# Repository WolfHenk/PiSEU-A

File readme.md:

THE SEU (Sende-Empfangs-Umsetzer) translates TW39 to ED1000 and vice versa

SEU-A was at "Amt" the networks side of the line. SEU-B was at the telex at costumers side.

This card emulates SEU-A and sits between raspberry Pi (piTelex) and a ED1000 and works as a kind of modem between piTelex TXD and RXD and Telex

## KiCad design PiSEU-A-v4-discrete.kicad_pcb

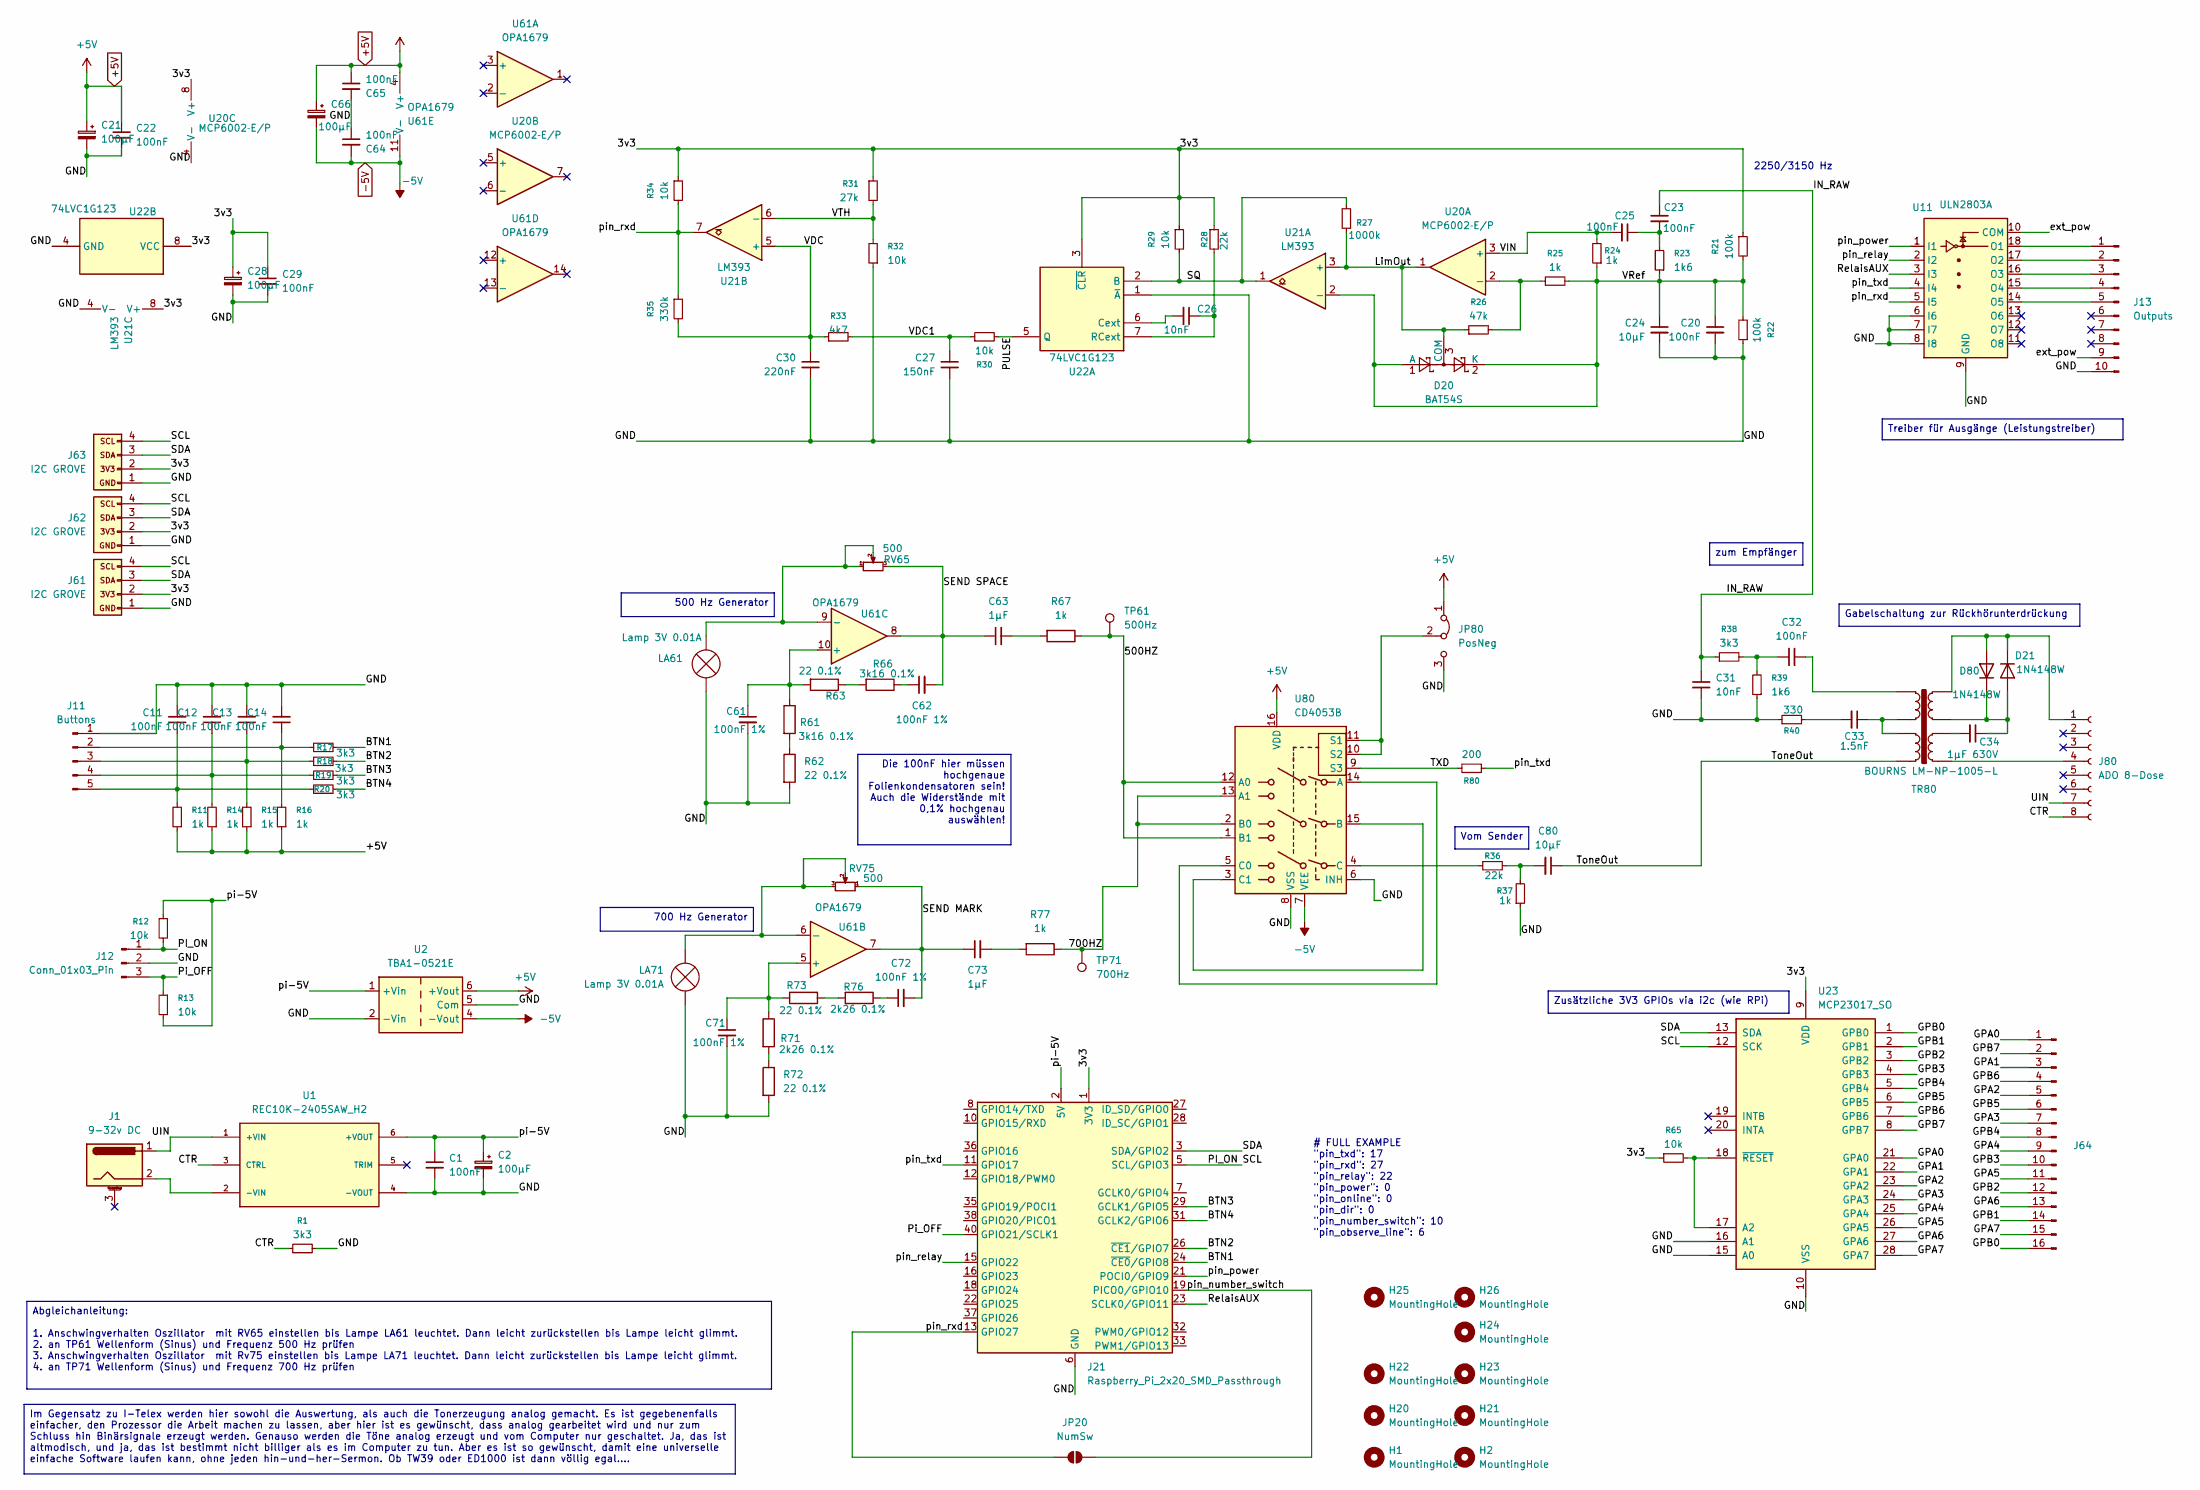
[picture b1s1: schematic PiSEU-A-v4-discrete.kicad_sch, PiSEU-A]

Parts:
C1, C11, C12, C13, C14, C20, C22, C23, C25, C29, C32, C64, C65: 100nF; C_Disc_D4.7mm_W2.5mm_P5.00mm; JLCPCB Part # C1590
C2, C21, C28: 100µF; CP_Radial_D6.3mm_P2.50mm; JLCPCB Part # C3338
C24, C80: 10µF; C_Radial_D5.0mm_H7.0mm_P2.00mm
C26, C31: 10nF; C_Disc_D5.0mm_W2.5mm_P2.50mm
C27: 150nF; C_Rect_L7.0mm_W4.5mm_P5.00mm; JLCPCB Part # C1597
C30: 220nF; C_Rect_L7.0mm_W4.5mm_P5.00mm; JLCPCB Part # C21120
C33: 1.5nF; C_Disc_D4.7mm_W2.5mm_P5.00mm; Part Number ggtt; JLCPCB Part # C1595
C34: 1µF 630V; C_Rect_L41.5mm_W15.0mm_P37.50mm_MKS4
C61, C62, C71, C72: 100nF 1%; C_Disc_D8.0mm_W2.5mm_P5.00mm
C63, C73: 1µF; C_Rect_L4.6mm_W3.8mm_P2.50mm_MKS02_FKP02; JLCPCB Part # C15849
C66: 100µF; CP_Radial_D6.3mm_P2.50mm
D20: BAT54S; SOT-23
D21, D80: 1N4148W; D_DO-35_SOD27_P7.62mm_Horizontal
H1, H2, H20, H21, H22, H23, H24, H25, H26: MountingHole; MountingHole_3.2mm_M3
J1: 9-32v DC; BarrelJack_Wuerth_6941xx301002
J11: Buttons; PinHeader_1x05_P2.54mm_Vertical
J12: Conn_01x03_Pin; PinHeader_1x03_P2.54mm_Vertical
J13: Outputs; PinHeader_2x05_P2.54mm_Vertical
J21: Raspberry_Pi_2x20_SMD_Passthrough; Raspberry_Pi_Zero_Socketed_THT_FaceDown_MountingHoles
J61, J62, J63: I2C GROVE; NS-Tech_Grove_1x04_P2mm_Vertical
J64: I2C-OUTPUTS; PinHeader_2x08_P2.54mm_Vertical; Part Number 1-1602FBV0T
J80: ADO 8-Dose; PinHeader_1x08_P2.54mm_Vertical
JP20: NumSw; SolderJumper-2_P1.3mm_Open_RoundedPad1.0x1.5mm
JP80: PosNeg; SolderJumper-3_P1.3mm_Bridged12_Pad1.0x1.5mm
LA61, LA71: Lamp 3V 0.01A; SolderWire-0.5sqmm_1x02_P4.6mm_D0.9mm_OD2.1mm
R1, R17, R18, R19, R20, R38: 3k3; R_Axial_DIN0207_L6.3mm_D2.5mm_P7.62mm_Horizontal; JLCPCB Part # C22978
R11, R14, R15, R16, R24, R25, R37, R67, R77: 1k; R_Axial_DIN0207_L6.3mm_D2.5mm_P7.62mm_Horizontal; JLCPCB Part # C21190
R12, R13, R29, R30, R32, R34, R65: 10k; R_Axial_DIN0207_L6.3mm_D2.5mm_P7.62mm_Horizontal; JLCPCB Part # C25804
R21, R22: 100k; R_Axial_DIN0207_L6.3mm_D2.5mm_P7.62mm_Horizontal; JLCPCB Part # C25803
R23, R39: 1k6; R_Axial_DIN0207_L6.3mm_D2.5mm_P7.62mm_Horizontal
R26: 47k; R_Axial_DIN0207_L6.3mm_D2.5mm_P7.62mm_Horizontal; JLCPCB Part # C25600
R27: 1000k; R_Axial_DIN0207_L6.3mm_D2.5mm_P7.62mm_Horizontal; JLCPCB Part # C22935
R28, R36: 22k; R_Axial_DIN0207_L6.3mm_D2.5mm_P7.62mm_Horizontal; JLCPCB Part # C31850
R31: 27k; R_Axial_DIN0207_L6.3mm_D2.5mm_P7.62mm_Horizontal; JLCPCB Part # C22967
R33: 4k7; R_Axial_DIN0207_L6.3mm_D2.5mm_P7.62mm_Horizontal
R35: 330k; R_Axial_DIN0207_L6.3mm_D2.5mm_P7.62mm_Horizontal
R40: 330; R_Axial_DIN0207_L6.3mm_D2.5mm_P7.62mm_Horizontal; JLCPCB Part # C23138
R61, R66: 3k16 0.1%; R_Axial_DIN0207_L6.3mm_D2.5mm_P7.62mm_Horizontal
R62, R63, R72, R73: 22 0.1%; R_Axial_DIN0207_L6.3mm_D2.5mm_P7.62mm_Horizontal
R71, R76: 2k26 0.1%; R_Axial_DIN0207_L6.3mm_D2.5mm_P7.62mm_Horizontal
R80: 200; R_Axial_DIN0207_L6.3mm_D2.5mm_P7.62mm_Horizontal; JLCPCB Part # C8218
RV65, RV75: 500; Potentiometer_Bourns_3386P_Vertical
TP61: 500Hz; TestPoint_Pad_1.0x1.0mm
TP71: 700Hz; TestPoint_Pad_1.0x1.0mm
TR80: BOURNS LM-NP-1005-L; TRANS_LM-NP-1005L_BRN
U1: REC10K-2405SAW_H2; CONV_REC10K-2405SAW_H2
U2: TBA1-0521E; Converter_DCDC_TRACO_TBA1-xxxxE_Dual_THT
U11: ULN2803A; DIP-18_W7.62mm_Socket
U20: MCP6002‑E/P; DIP-8_W7.62mm_Socket
U21: LM393; DIP-8_W7.62mm_Socket
U22: 74LVC1G123; SSOP-8_3.9x5.05mm_P1.27mm
U23: MCP23017_SO; SOIC-28W_7.5x17.9mm_P1.27mm
U61: OPA1679; SOIC-14_3.9x8.7mm_P1.27mm
U80: CD4053B; SOIC-16_3.9x9.9mm_P1.27mm; JLCPCB Part # C6742

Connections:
+5V: C21.1, C22.1, C65.1, C66.1, JP80.1 (A), R11.1, R14.1, R15.1, R16.1, U2.6 (+Vout), U61.4 (V+), U80.16 (VDD)
-5V: C64.2, C66.2, U2.4 (-Vout), U61.11 (V-), U80.7 (VEE)
/3v3: C28.1, C29.1, J21.1 (3V3), J21.17 (3V3), J61.2, J62.2, J63.2, R21.1, R28.1, R29.1, R31.1, R34.1, R65.1, U20.8 (V+), U21.8 (V+), U22.3 (~CLR), U22.8 (VCC), U23.9 (VDD)
/500HZ: R67.1, TP61.1, U80.1 (B1), U80.12 (A0)
/700HZ: R77.1, TP71.1, U80.2 (B0), U80.13 (A1)
/BTN1: J21.24 (~CE0/GPIO8), R17.2
/BTN2: J21.26 (~CE1/GPIO7), R18.2
/BTN3: J21.29 (GCLK1/GPIO5), R19.2
/BTN4: J21.31 (GCLK2/GPIO6), R20.2
/CTR: J80.8, R1.1, U1.3 (CTRL)
/GND: C1.2, C2.2, C11.2, C12.2, C13.2, C14.2, C20.2, C21.2, C22.2, C24.2, C27.2, C28.2, C29.2, C30.2, C31.2, C61.2, C64.1, C65.2, C71.2, J11.1, J12.2, J13.10, J21.6 (GND), J21.9 (GND), J21.14 (GND), J21.20 (GND), J21.25 (GND), J21.30 (GND), J21.34 (GND), J21.39 (GND), J61.1, J62.1, J63.1, JP80.3 (B), LA61.1 (-), LA71.1 (-), R1.2, R22.1, R32.1, R37.1, R39.1, R40.1, R62.2, R72.2, U1.4 (-VOUT), U2.2 (-Vin), U2.5 (Com), U11.6 (I6), U11.7 (I7), U11.8 (I8), U11.9 (GND), U20.4 (V-), U21.4 (V-), U22.1 (~A), U22.4 (GND), U23.10 (VSS), U23.15 (A0), U23.16 (A1), U80.6 (INH), U80.8 (VSS)
/GPA0: J64.1, U23.21 (GPA0)
/GPA1: J64.3, U23.22 (GPA1)
/GPA2: J64.5, U23.23 (GPA2)
/GPA3: J64.7, U23.24 (GPA3)
/GPA4: J64.9, U23.25 (GPA4)
/GPA5: J64.11, U23.26 (GPA5)
/GPA6: J64.13, U23.27 (GPA6)
/GPA7: J64.15, U23.28 (GPA7)
/GPB0: J64.16, U23.1 (GPB0)
/GPB1: J64.14, U23.2 (GPB1)
/GPB2: J64.12, U23.3 (GPB2)
/GPB3: J64.10, U23.4 (GPB3)
/GPB4: J64.8, U23.5 (GPB4)
/GPB5: J64.6, U23.6 (GPB5)
/GPB6: J64.4, U23.7 (GPB6)
/GPB7: J64.2, U23.8 (GPB7)
/IN_RAW: C23.1, C31.1, R38.1
/LimOut: D20.3 (COM), R26.1, R27.1, U20.1, U21.3 (+)
/PI_ON: J12.1, J21.5 (SCL/GPIO3), J61.4, J62.4, J63.4, R12.2, U23.12 (SCK)
/PULSE: R30.2, U22.5 (Q)
/Pi_OFF: J12.3, J21.40 (GPIO21/SCLK1), R13.1
/RelaisAUX: J21.23 (SCLK0/GPIO11), U11.3 (I3)
/SDA: J21.3 (SDA/GPIO2), J61.3, J62.3, J63.3, U23.13 (SDA)
/SEND MARK: C72.2, C73.1, RV75.1, U61.7
/SEND SPACE: C62.2, C63.1, RV65.3, U61.8
/SQ: R27.2, R29.2, U21.1, U22.2 (B)
/TXD: R80.2, U80.9 (S3)
/ToneOut: C80.1, TR80.8
/UIN: J1.1, J80.7, U1.1 (+VIN)
/VDC: C30.1, R33.1, R35.2, U21.5 (+)
/VDC1: C27.1, R30.1, R33.2
/VIN: C25.2, R24.2, U20.3 (+)
/VRef: C20.1, C24.1, D20.1 (A), D20.2 (K), R21.2, R22.2, R23.1, R24.1, R25.2, U21.2 (-)
/VTH: R31.2, R32.2, U21.6 (-)
/ext_pow: J13.9, U11.10 (COM)
/pi-5V: C1.1, C2.1, J21.2 (5V), J21.4 (5V), R12.1, R13.2, U1.6 (+VOUT), U2.1 (+Vin)
/pin_number_switch: J21.19 (PICO0/GPIO10), JP20.2 (B)
/pin_power: J21.21 (POCI0/GPIO9), U11.1 (I1)
/pin_relay: J21.15 (GPIO22), U11.2 (I2)
/pin_rxd: J21.13 (GPIO27), JP20.1 (A), R34.2, R35.1, U11.5 (I5), U21.7
/pin_txd: J21.11 (GPIO17), R80.1, U11.4 (I4)
unnamed: C23.2, C25.1, R23.2
unnamed: C32.1, TR80.5
unnamed: C32.2, R38.2, R39.2
unnamed: C33.1, TR80.6, TR80.7
unnamed: C33.2, R40.2
unnamed: C34.2, TR80.2
unnamed: C62.1, R66.1
unnamed: C63.2, R67.2
unnamed: C72.1, R76.1
unnamed: C73.2, R77.2
unnamed: C80.2, R36.2, R37.2
unnamed: C34.1, D21.2 (A), D80.1 (K), TR80.3
unnamed: D21.1 (K), D80.2 (A), J80.1, TR80.4
unnamed: C14.1, J11.2, R16.2, R17.1
unnamed: C13.1, J11.3, R15.2, R18.1
unnamed: C12.1, J11.4, R14.2, R19.1
unnamed: C11.1, J11.5, R11.2, R20.1
unnamed: J13.1, U11.18 (O1)
unnamed: J13.2, U11.17 (O2)
unnamed: J13.3, U11.16 (O3)
unnamed: J13.4, U11.15 (O4)
unnamed: J13.5, U11.14 (O5)
unnamed: J80.4, TR80.1
unnamed: JP80.2 (C), U80.10 (S2), U80.11 (S1)
unnamed: LA61.2 (+), RV65.1, RV65.2, U61.9 (-)
unnamed: LA71.2 (+), RV75.2, RV75.3, U61.6 (-)
unnamed: R61.2, R62.1
unnamed: R63.1, R66.2
unnamed: R71.2, R72.1
unnamed: R73.1, R76.2
unnamed: J1.2, U1.2 (-VIN)
unnamed: R25.1, R26.2, U20.2 (-)
unnamed: C26.2, U22.6 (Cext)
unnamed: C26.1, R28.2, U22.7 (RCext)
unnamed: R65.2, U23.17 (A2), U23.18 (~RESET)
unnamed: C71.1, R71.1, R73.2, U61.5 (+)
unnamed: C61.1, R61.1, R63.2, U61.10 (+)
unnamed: U80.5 (C0), U80.14 (A)
unnamed: U80.3 (C1), U80.15 (B)
unnamed: R36.1, U80.4 (C)

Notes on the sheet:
# FULL EXAMPLE "pin_txd": 17 "pin_rxd": 27 "pin_relay": 22 "pin_power": 0 "pin_online": 0 "pin_dir": 0 "pin_number_switch": 10 "pin_observe_line": 6
2250/3150 Hz
Zusätzliche 3V3 GPIOs via i2c (wie RPi)
Die 100nF hier müssen hochgenaue Folienkondensatoren sein! Auch die Widerstände mit 0,1% hochgenau auswählen!
500 Hz Generator
Im Gegensatz zu I-Telex werden hier sowohl die Auswertung, als auch die Tonerzeugung analog gemacht. Es ist gegebenenfalls einfacher, den Prozessor die Arbeit machen zu lassen, aber hier ist es gewünscht, dass analog gearbeitet wird und nur zum Schluss hin Binärsignale erzeugt werden. Genauso werde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
Vom Sender
zum Empfänger
Abgleichanleitung: 1. Anschwingverhalten Oszillator mit RV65 einstellen bis Lampe LA61 leuchtet. Dann leicht zurückstellen bis Lampe leicht glimmt. 2. an TP61 Wellenform (Sinus) und Frequenz 500 Hz prüfen 3. Anschwingverhalten Oszillator mit Rv75 einstellen bis Lampe LA71 leuchtet. Dann leicht zurü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
Treiber für Ausgänge (Leistungstreiber)
Gabelschaltung zur Rückhörunterdrückung
700 Hz Generator

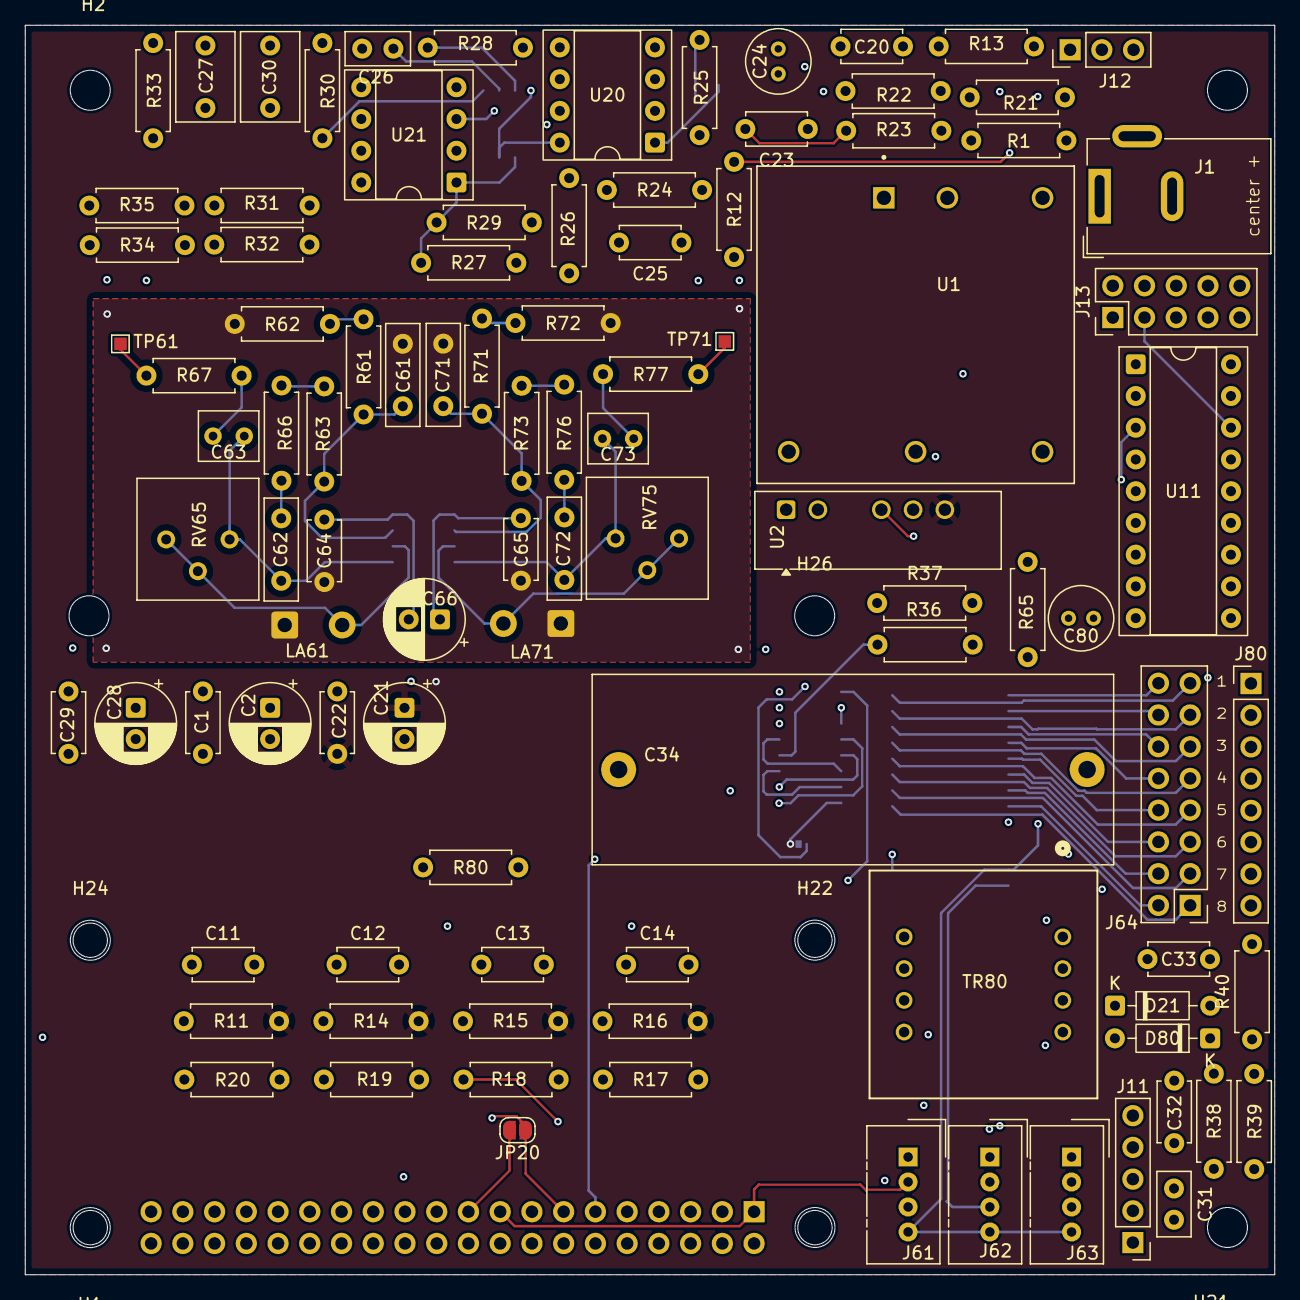
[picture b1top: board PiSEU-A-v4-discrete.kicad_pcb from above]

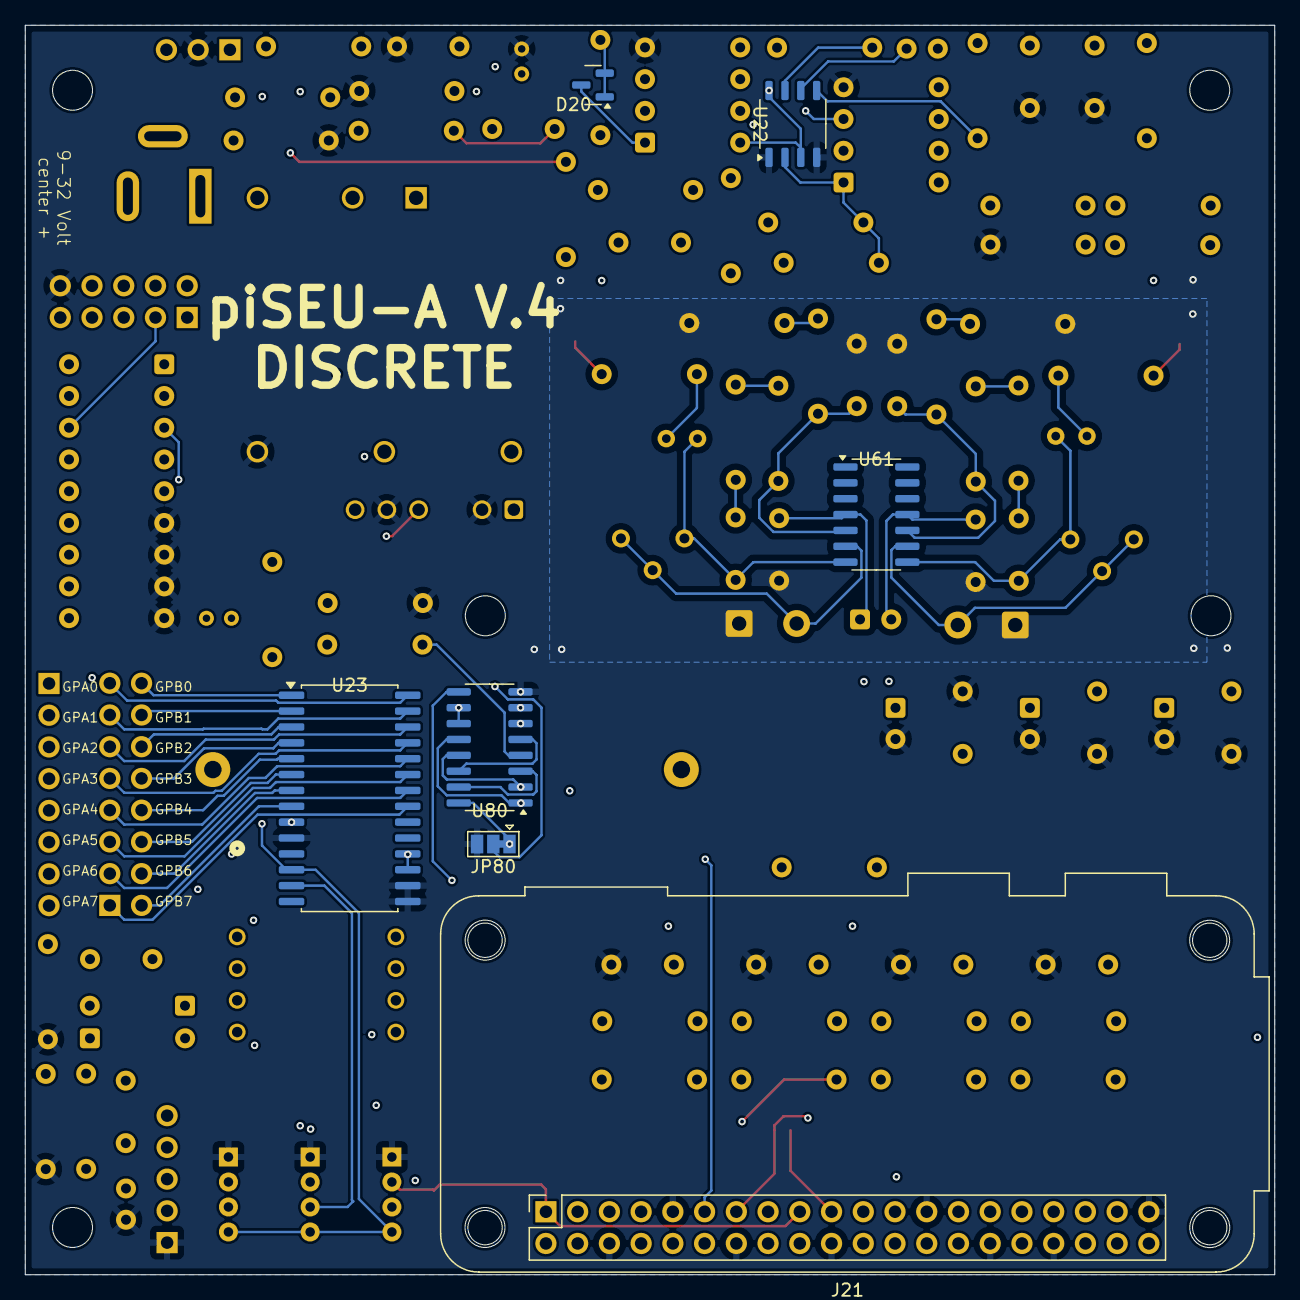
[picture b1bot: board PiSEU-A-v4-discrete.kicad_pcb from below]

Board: 4 copper layers, 100.0 x 100.0 mm, 114 parts (7 on the bottom side), 92 nets.

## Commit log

2026-02-09 Add introduction for SEU device functionality
2026-02-09 Rename intro.txt to readme.md
2026-02-09 Fix typo in SEU-A description in readme.md
